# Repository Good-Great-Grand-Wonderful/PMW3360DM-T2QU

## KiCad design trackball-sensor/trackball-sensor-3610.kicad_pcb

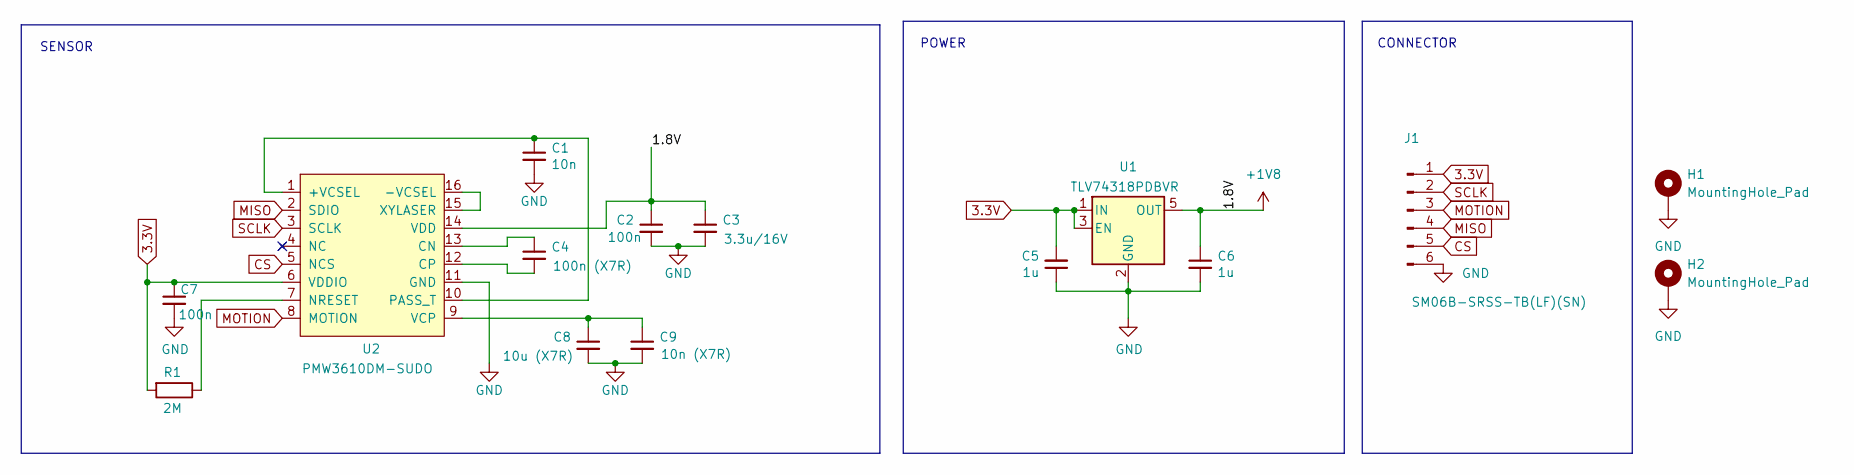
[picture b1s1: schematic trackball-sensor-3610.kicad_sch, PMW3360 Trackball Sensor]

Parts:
C1: 10n; C_0603_1608Metric; LCSC C57112
C2, C7: 100n; C_0603_1608Metric; LCSC C14663
C3: 3.3u/16V; C_0603_1608Metric; LCSC C342962
C4: 100n (X7R); C_0603_1608Metric; LCSC C14663
C5, C6: 1u; C_0603_1608Metric; LCSC C15849
C8: 10u (X7R); C_0603_1608Metric; LCSC C237435
C9: 10n (X7R); C_0603_1608Metric; LCSC C57112
H1, H2: MountingHole_Pad; MountingHole_3.2mm_M3_Pad
J1: SM06B-SRSS-TB(LF)(SN); JST_SH_SM06B-SRSS-TB_1x06-1MP_P1.00mm_Horizontal
R1: 2M; R_0603_1608Metric; LCSC C22976
U1: TLV74318PDBVR; SOT-23-5; LCSC C485152
U2: PMW3610DM-SUDO; PMW3610DM-SUDU 16Pin

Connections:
3.3V: C5.2, C7.1, J1.1, R1.2, U1.1 (IN), U1.3 (EN), U2.6 (VDDIO)
+1V8: C2.1, C3.1, C6.1, U1.5 (OUT), U2.14 (VDD)
CS: J1.5, U2.5 (NCS)
GND: C1.2, C2.2, C3.2, C5.1, C6.2, C7.2, C8.2, C9.2, H1.1, H2.1, J1.6, U1.2 (GND), U2.11 (GND)
MISO: J1.4, U2.2 (SDIO)
MOTION: J1.3, U2.8 (MOTION)
unnamed: C1.1, U2.1 (+VCSEL), U2.10 (PASS_T)
unnamed: U2.15 (XYLASER), U2.16 (-VCSEL)
unnamed: C4.1, U2.13 (CN)
unnamed: C4.2, U2.12 (CP)
unnamed: R1.1, U2.7 (NRESET)
unnamed: C8.1, C9.1, U2.9 (VCP)
SCLK: J1.2, U2.3 (SCLK)

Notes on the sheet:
SENSOR
POWER
CONNECTOR

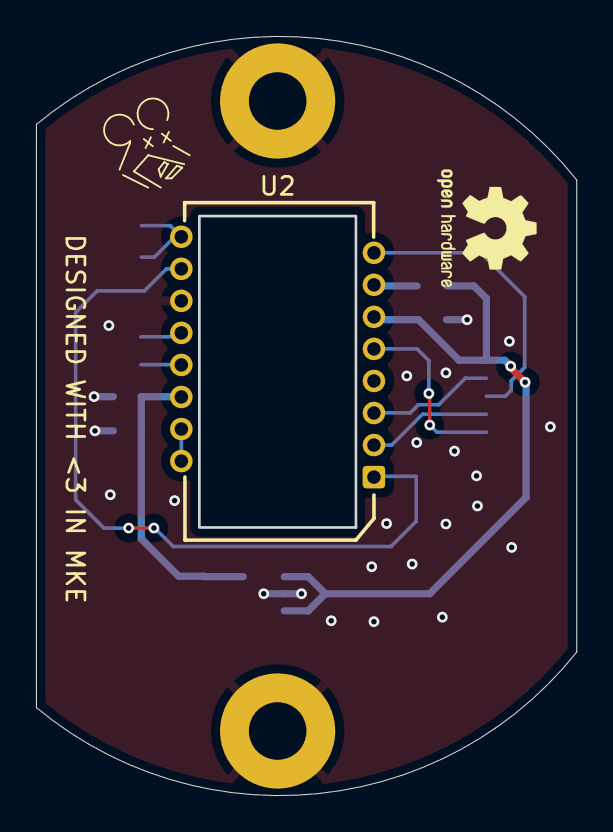
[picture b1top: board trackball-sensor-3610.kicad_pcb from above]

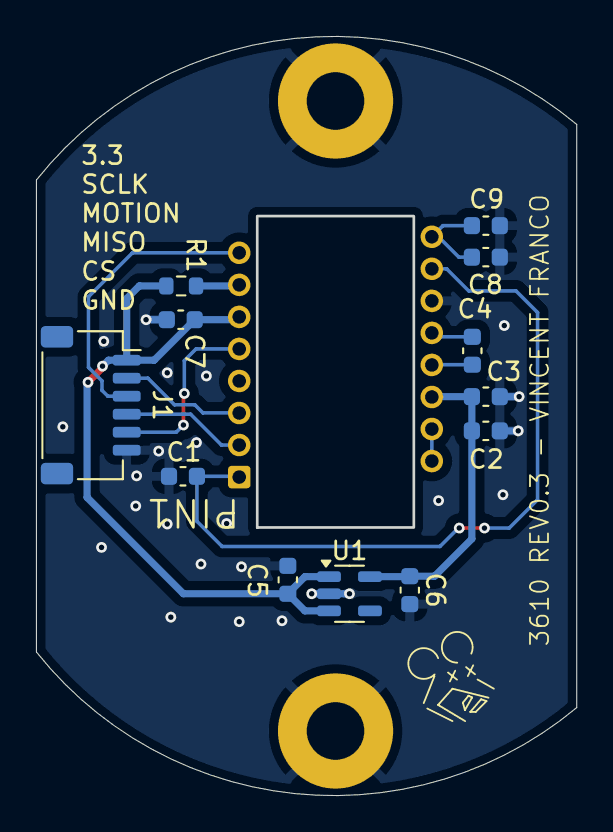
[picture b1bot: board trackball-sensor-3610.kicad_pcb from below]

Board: 2 copper layers, 29.9 x 42.1 mm, 15 parts (12 on the bottom side), 13 nets.

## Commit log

2025-06-23 Adding 3610
2025-06-23 Pin1 label
